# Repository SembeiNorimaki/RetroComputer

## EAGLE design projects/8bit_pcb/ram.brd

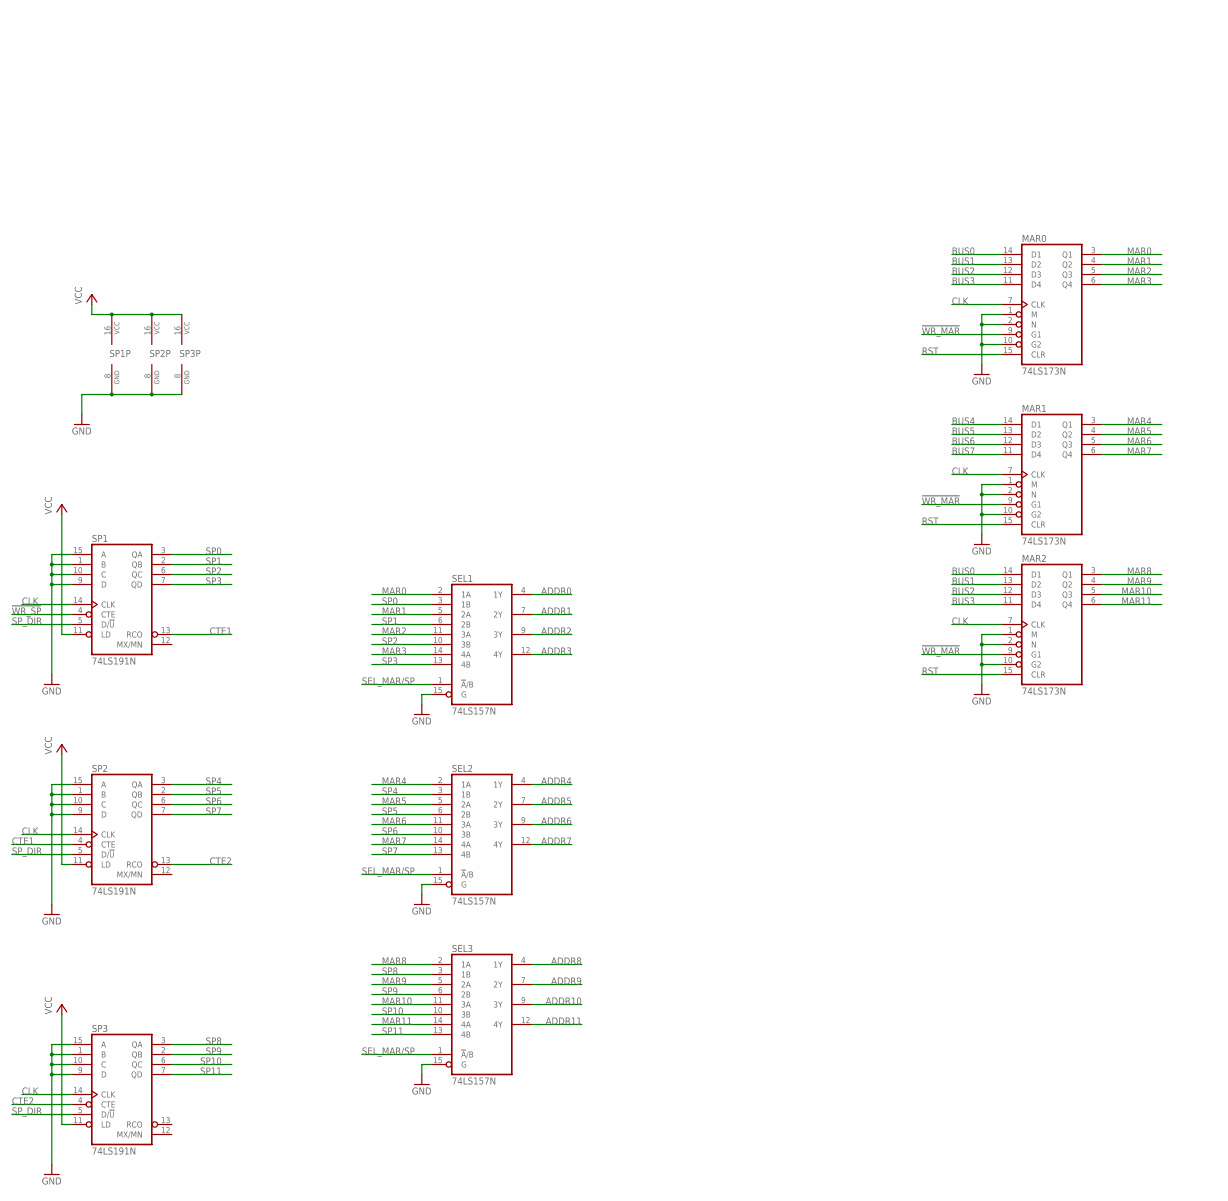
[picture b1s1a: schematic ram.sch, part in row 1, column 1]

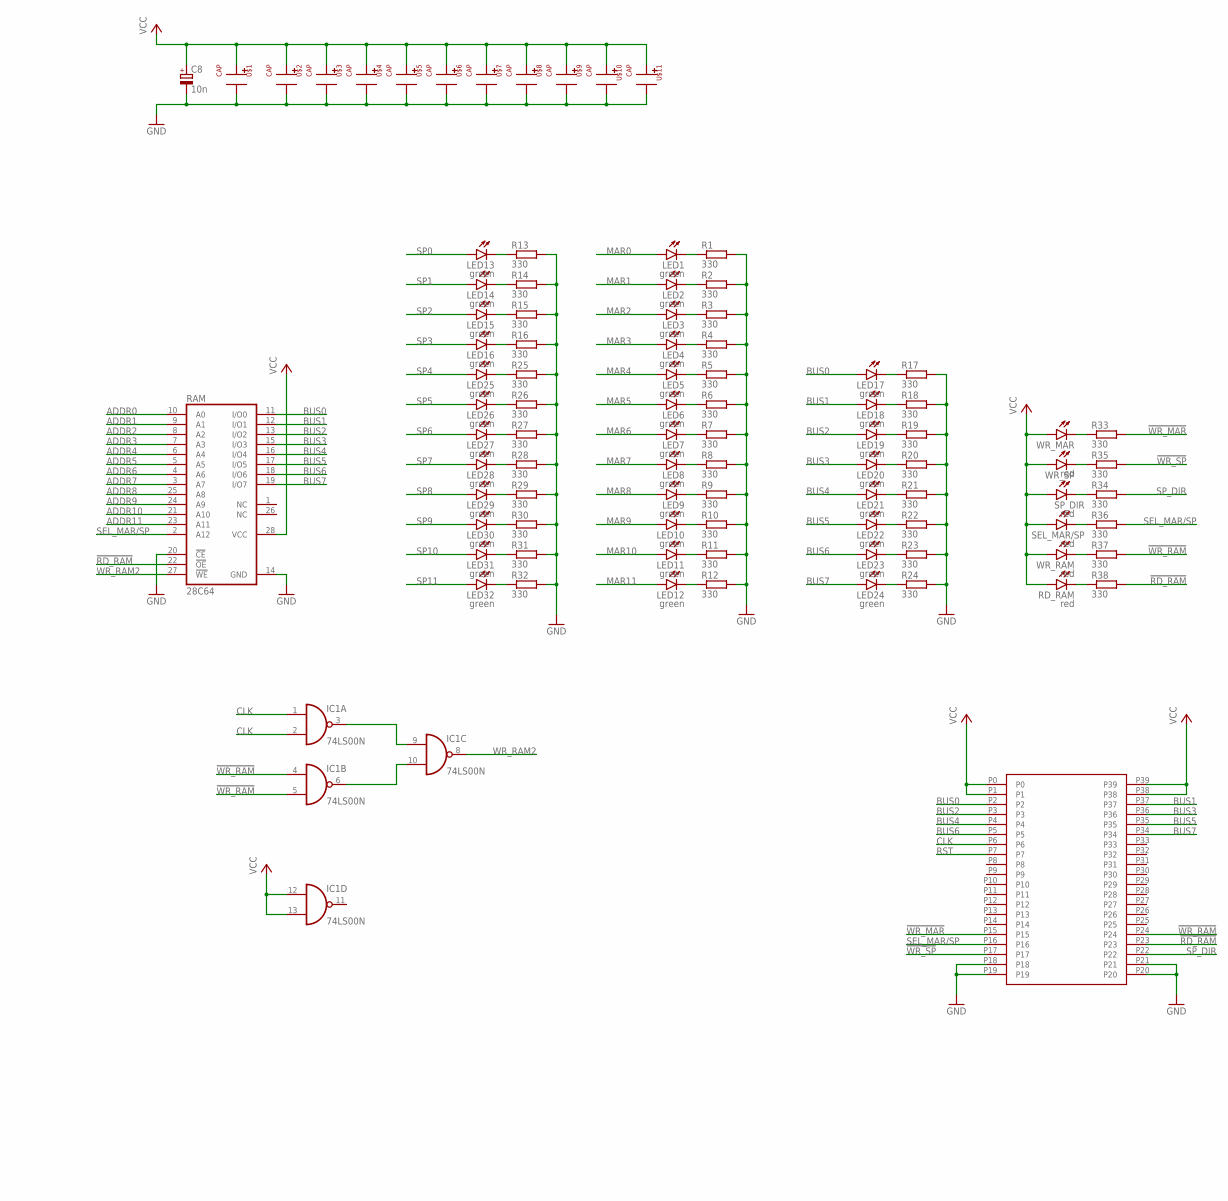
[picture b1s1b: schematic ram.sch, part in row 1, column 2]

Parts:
C8: 10n; E2,5-6E
IC1: 74LS00N; DIL14
LED1, LED2, LED3, LED4, LED5, LED6, LED7, LED8, LED9, LED10, LED11, LED12, LED13, LED14, LED15, LED16, LED17, LED18, LED19, LED20, LED21, LED22, LED23, LED24, LED25, LED26, LED27, LED28, LED29, LED30, LED31, LED32: green; SML1206
MAR0, MAR1, MAR2: 74LS173N; DIL16
R1, R2, R3, R4, R5, R6, R7, R8, R9, R10, R11, R12, R13, R14, R15, R16, R17, R18, R19, R20, R21, R22, R23, R24, R25, R26, R27, R28, R29, R30, R31, R32, R33, R34, R35, R36, R37, R38: 330; R0805
RAM: 28C64; DIL28-6
RD_RAM: red; SML1206
SEL1, SEL2, SEL3: 74LS157N; DIL16
SEL_MAR/SP: red; SML1206
SP1, SP2, SP3: 74LS191N; DIL16
SP_DIR: red; SML1206
U$1, U$2, U$3, U$4, U$5, U$6, U$7, U$8, U$9, U$10, U$11: CAP
U$12: 2X40
WR_MAR: red; SML1206
WR_RAM: red; SML1206
WR_SP: red; SML1206

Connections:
!RD_RAM: R38.2, RAM.22 (!OE), U$12.P23
!WR_MAR: MAR0.9 (G1), MAR1.9 (G1), MAR2.9 (G1), R33.2, U$12.P15
!WR_RAM: IC1.4 (I0), IC1.5 (I1), R37.2, U$12.P24
!WR_SP: R35.2, SP1.4 (CTE), U$12.P17
ADDR0: RAM.10 (A0), SEL1.4 (1Y)
ADDR1: RAM.9 (A1), SEL1.7 (2Y)
ADDR2: RAM.8 (A2), SEL1.9 (3Y)
ADDR3: RAM.7 (A3), SEL1.12 (4Y)
ADDR4: RAM.6 (A4), SEL2.4 (1Y)
ADDR5: RAM.5 (A5), SEL2.7 (2Y)
ADDR6: RAM.4 (A6), SEL2.9 (3Y)
ADDR7: RAM.3 (A7), SEL2.12 (4Y)
ADDR8: RAM.25 (A8), SEL3.4 (1Y)
ADDR9: RAM.24 (A9), SEL3.7 (2Y)
ADDR10: RAM.21 (A10), SEL3.9 (3Y)
ADDR11: RAM.23 (A11), SEL3.12 (4Y)
BUS0: LED17.A, MAR0.14 (D1), MAR2.14 (D1), RAM.11 (I/O0), U$12.P2
BUS1: LED18.A, MAR0.13 (D2), MAR2.13 (D2), RAM.12 (I/O1), U$12.P37
BUS2: LED19.A, MAR0.12 (D3), MAR2.12 (D3), RAM.13 (I/O2), U$12.P3
BUS3: LED20.A, MAR0.11 (D4), MAR2.11 (D4), RAM.15 (I/O3), U$12.P36
BUS4: LED21.A, MAR1.14 (D1), RAM.16 (I/O4), U$12.P4
BUS5: LED22.A, MAR1.13 (D2), RAM.17 (I/O5), U$12.P35
BUS6: LED23.A, MAR1.12 (D3), RAM.18 (I/O6), U$12.P5
BUS7: LED24.A, MAR1.11 (D4), RAM.19 (I/O7), U$12.P34
CLK: IC1.1 (I0), IC1.2 (I1), MAR0.7 (CLK), MAR1.7 (CLK), MAR2.7 (CLK), SP1.14 (CLK), SP2.14 (CLK), SP3.14 (CLK), U$12.P6
CTE1: SP1.13 (RCO), SP2.4 (CTE)
CTE2: SP2.13 (RCO), SP3.4 (CTE)
GND: C8.-, IC1.7 (GND), MAR0.1 (M), MAR0.2 (N), MAR0.8 (GND), MAR0.10 (G2), MAR1.1 (M), MAR1.2 (N), MAR1.8 (GND), MAR1.10 (G2), MAR2.1 (M), MAR2.2 (N), MAR2.8 (GND), MAR2.10 (G2), R1.2, R2.2, R3.2, R4.2, R5.2, R6.2, R7.2, R8.2, R9.2, R10.2, R11.2, R12.2, R13.2, R14.2, R15.2, R16.2, R17.2, R18.2, R19.2, R20.2, R21.2, R22.2, R23.2, R24.2, R25.2, R26.2, R27.2, R28.2, R29.2, R30.2, R31.2, R32.2, RAM.14 (GND), RAM.20 (!CE), SEL1.8 (GND), SEL1.15 (G), SEL2.8 (GND), SEL2.15 (G), SEL3.8 (GND), SEL3.15 (G), SP1.1 (B), SP1.8 (GND), SP1.9 (D), SP1.10 (C), SP1.15 (A), SP2.1 (B), SP2.8 (GND), SP2.9 (D), SP2.10 (C), SP2.15 (A), SP3.1 (B), SP3.8 (GND), SP3.9 (D), SP3.10 (C), SP3.15 (A), U$1.P-, U$2.P-, U$3.P-, U$4.P-, U$5.P-, U$6.P-, U$7.P-, U$8.P-, U$9.P-, U$10.P-, U$11.P-, U$12.P18, U$12.P19, U$12.P20, U$12.P21
MAR0: LED1.A, MAR0.3 (Q1), SEL1.2 (1A)
MAR1: LED2.A, MAR0.4 (Q2), SEL1.5 (2A)
MAR2: LED3.A, MAR0.5 (Q3), SEL1.11 (3A)
MAR3: LED4.A, MAR0.6 (Q4), SEL1.14 (4A)
MAR4: LED5.A, MAR1.3 (Q1), SEL2.2 (1A)
MAR5: LED6.A, MAR1.4 (Q2), SEL2.5 (2A)
MAR6: LED7.A, MAR1.5 (Q3), SEL2.11 (3A)
MAR7: LED8.A, MAR1.6 (Q4), SEL2.14 (4A)
MAR8: LED9.A, MAR2.3 (Q1), SEL3.2 (1A)
MAR9: LED10.A, MAR2.4 (Q2), SEL3.5 (2A)
MAR10: LED11.A, MAR2.5 (Q3), SEL3.11 (3A)
MAR11: LED12.A, MAR2.6 (Q4), SEL3.14 (4A)
unnamed: LED1.C, R1.1
unnamed: LED2.C, R2.1
unnamed: LED3.C, R3.1
unnamed: LED4.C, R4.1
unnamed: LED5.C, R5.1
unnamed: LED6.C, R6.1
unnamed: LED7.C, R7.1
unnamed: LED8.C, R8.1
unnamed: LED13.C, R13.1
unnamed: LED9.C, R9.1
unnamed: LED10.C, R10.1
unnamed: LED11.C, R11.1
unnamed: LED12.C, R12.1
unnamed: LED14.C, R14.1
unnamed: LED15.C, R15.1
unnamed: LED16.C, R16.1
unnamed: LED25.C, R25.1
unnamed: LED26.C, R26.1
unnamed: LED17.C, R17.1
unnamed: LED18.C, R18.1
unnamed: LED19.C, R19.1
unnamed: LED20.C, R20.1
unnamed: LED21.C, R21.1
unnamed: LED22.C, R22.1
unnamed: LED23.C, R23.1
unnamed: LED24.C, R24.1
unnamed: LED27.C, R27.1
unnamed: LED28.C, R28.1
unnamed: LED29.C, R29.1
unnamed: LED30.C, R30.1
unnamed: LED31.C, R31.1
unnamed: LED32.C, R32.1
unnamed: IC1.3 (O), IC1.9 (I0)
unnamed: IC1.6 (O), IC1.10 (I1)
unnamed: R36.1, SEL_MAR/SP.C
unnamed: R33.1, WR_MAR.C
unnamed: R34.1, SP_DIR.C
unnamed: R35.1, WR_SP.C
unnamed: R37.1, WR_RAM.C
unnamed: R38.1, RD_RAM.C
RST: MAR0.15 (CLR), MAR1.15 (CLR), MAR2.15 (CLR), U$12.P7
SEL_MAR/SP: R36.2, RAM.2 (A12), SEL1.1 (!A!/B), SEL2.1 (!A!/B), SEL3.1 (!A!/B), U$12.P16
SP0: LED13.A, SEL1.3 (1B), SP1.3 (QA)
SP1: LED14.A, SEL1.6 (2B), SP1.2 (QB)
SP2: LED15.A, SEL1.10 (3B), SP1.6 (QC)
SP3: LED16.A, SEL1.13 (4B), SP1.7 (QD)
SP4: LED25.A, SEL2.3 (1B), SP2.3 (QA)
SP5: LED26.A, SEL2.6 (2B), SP2.2 (QB)
SP6: LED27.A, SEL2.10 (3B), SP2.6 (QC)
SP7: LED28.A, SEL2.13 (4B), SP2.7 (QD)
SP8: LED29.A, SEL3.3 (1B), SP3.3 (QA)
SP9: LED30.A, SEL3.6 (2B), SP3.2 (QB)
SP10: LED31.A, SEL3.10 (3B), SP3.6 (QC)
SP11: LED32.A, SEL3.13 (4B), SP3.7 (QD)
SP_DIR: R34.2, SP1.5 (D/!U), SP2.5 (D/!U), SP3.5 (D/!U), U$12.P22
VCC: C8.+, IC1.12 (I0), IC1.13 (I1), IC1.14 (VCC), MAR0.16 (VCC), MAR1.16 (VCC), MAR2.16 (VCC), RAM.28 (VCC), RD_RAM.A, SEL1.16 (VCC), SEL2.16 (VCC), SEL3.16 (VCC), SEL_MAR/SP.A, SP1.11 (LD), SP1.16 (VCC), SP2.11 (LD), SP2.16 (VCC), SP3.11 (LD), SP3.16 (VCC), SP_DIR.A, U$1.P+, U$2.P+, U$3.P+, U$4.P+, U$5.P+, U$6.P+, U$7.P+, U$8.P+, U$9.P+, U$10.P+, U$11.P+, U$12.P0, U$12.P1, U$12.P38, U$12.P39, WR_MAR.A, WR_RAM.A, WR_SP.A
WR_RAM2: IC1.8 (O), RAM.27 (!WE)

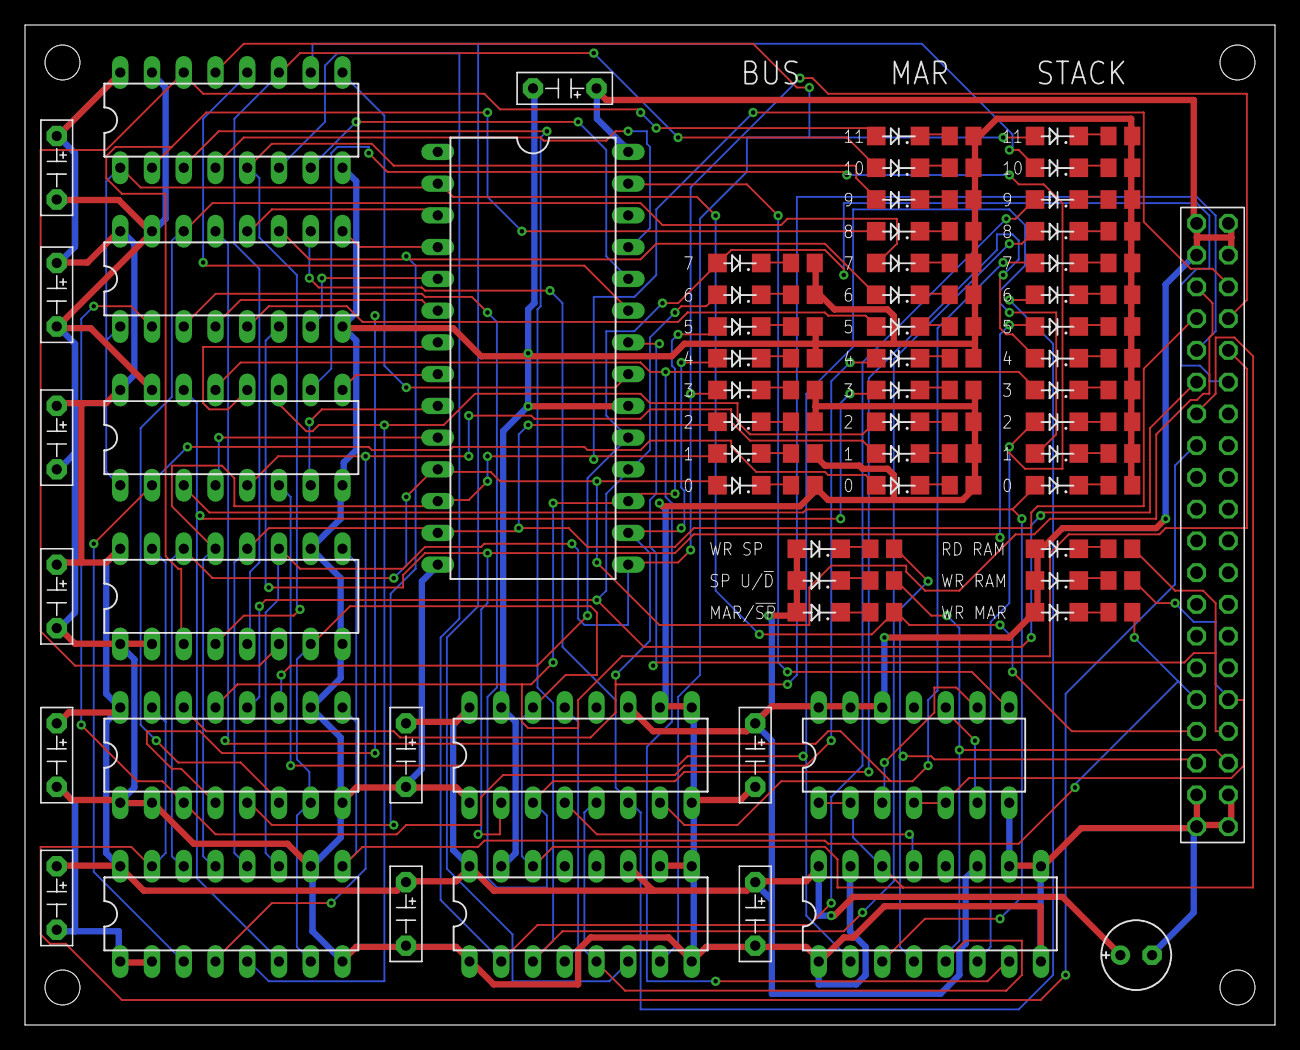
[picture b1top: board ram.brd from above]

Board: 2 copper layers, 100.0 x 80.0 mm, 100 parts (0 on the bottom side), 97 nets.

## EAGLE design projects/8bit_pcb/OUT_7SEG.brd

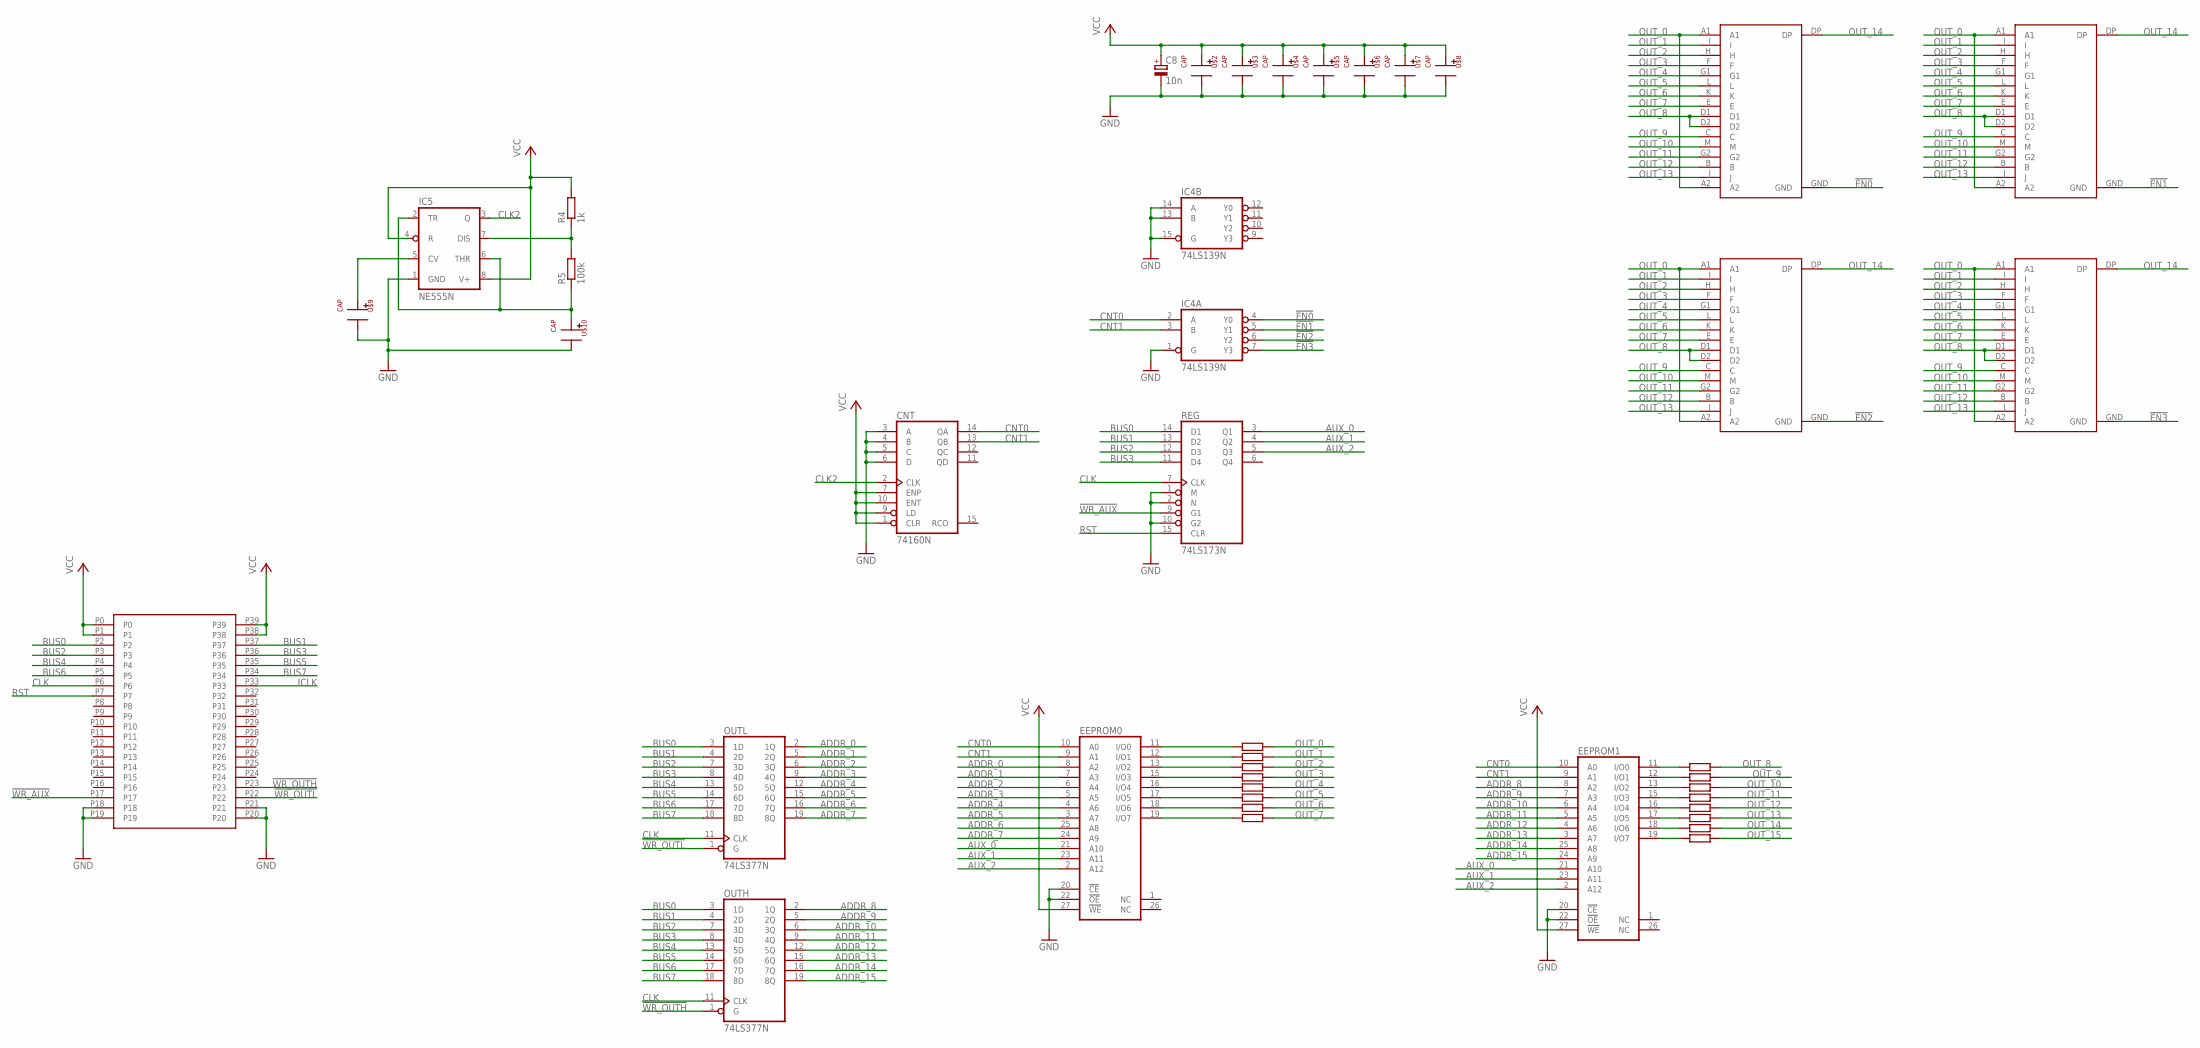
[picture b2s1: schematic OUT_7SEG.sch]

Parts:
C8: 10n; E2,5-6E
CNT: 74160N; DIL16
DISP1, DISP2, DISP3, DISP4: 16SEG
EEPROM0, EEPROM1: 78C64P; DIL28-6
IC4: 74LS139N; DIL16
IC5: NE555N; DIL08
OUTH: 74LS377N; DIL20
OUTL: 74LS377N; DIL20
R1, R2, R3, R6, R7, R8, R9, R10, R11, R12, R13, R14, R15, R16, R17, R41: 330; R0805
R4: 1k; 0204/7
R5: 100k; 0204/7
REG: 74LS173N; DIL16
U$1: 2X40
U$2, U$3, U$4, U$5, U$6, U$7, U$8, U$9, U$10: CAP

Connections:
!EN0: DISP1.GND, IC4.4 (Y0)
!EN1: DISP2.GND, IC4.5 (Y1)
!EN2: DISP3.GND, IC4.6 (Y2)
!EN3: DISP4.GND, IC4.7 (Y3)
!WR_AUX: REG.9 (G1), U$1.P17
!WR_OUTH: OUTH.1 (G), U$1.P23
!WR_OUTL: OUTL.1 (G), U$1.P22
ADDR_0: EEPROM0.8 (A2), OUTL.2 (1Q)
ADDR_1: EEPROM0.7 (A3), OUTL.5 (2Q)
ADDR_2: EEPROM0.6 (A4), OUTL.6 (3Q)
ADDR_3: EEPROM0.5 (A5), OUTL.9 (4Q)
ADDR_4: EEPROM0.4 (A6), OUTL.12 (5Q)
ADDR_5: EEPROM0.3 (A7), OUTL.15 (6Q)
ADDR_6: EEPROM0.25 (A8), OUTL.16 (7Q)
ADDR_7: EEPROM0.24 (A9), OUTL.19 (8Q)
ADDR_8: EEPROM1.8 (A2), OUTH.2 (1Q)
ADDR_9: EEPROM1.7 (A3), OUTH.5 (2Q)
ADDR_10: EEPROM1.6 (A4), OUTH.6 (3Q)
ADDR_11: EEPROM1.5 (A5), OUTH.9 (4Q)
ADDR_12: EEPROM1.4 (A6), OUTH.12 (5Q)
ADDR_13: EEPROM1.3 (A7), OUTH.15 (6Q)
ADDR_14: EEPROM1.25 (A8), OUTH.16 (7Q)
ADDR_15: EEPROM1.24 (A9), OUTH.19 (8Q)
AUX_0: EEPROM0.21 (A10), EEPROM1.21 (A10), REG.3 (Q1)
AUX_1: EEPROM0.23 (A11), EEPROM1.23 (A11), REG.4 (Q2)
AUX_2: EEPROM0.2 (A12), EEPROM1.2 (A12), REG.5 (Q3)
BUS0: OUTH.3 (1D), OUTL.3 (1D), REG.14 (D1), U$1.P2
BUS1: OUTH.4 (2D), OUTL.4 (2D), REG.13 (D2), U$1.P37
BUS2: OUTH.7 (3D), OUTL.7 (3D), REG.12 (D3), U$1.P3
BUS3: OUTH.8 (4D), OUTL.8 (4D), REG.11 (D4), U$1.P36
BUS4: OUTH.13 (5D), OUTL.13 (5D), U$1.P4
BUS5: OUTH.14 (6D), OUTL.14 (6D), U$1.P35
BUS6: OUTH.17 (7D), OUTL.17 (7D), U$1.P5
BUS7: OUTH.18 (8D), OUTL.18 (8D), U$1.P34
CLK: OUTH.11 (CLK), OUTL.11 (CLK), REG.7 (CLK), U$1.P6
CLK2: CNT.2 (CLK), IC5.3 (Q)
CNT0: CNT.14 (QA), EEPROM0.10 (A0), EEPROM1.10 (A0), IC4.2 (A)
CNT1: CNT.13 (QB), EEPROM0.9 (A1), EEPROM1.9 (A1), IC4.3 (B)
GND: C8.-, CNT.3 (A), CNT.4 (B), CNT.5 (C), CNT.6 (D), CNT.8 (GND), EEPROM0.14 (GND), EEPROM0.20 (!CE), EEPROM0.22 (!OE), EEPROM1.14 (GND), EEPROM1.20 (!CE), EEPROM1.22 (!OE), IC4.1 (G), IC4.8 (GND), IC4.13 (B), IC4.14 (A), IC4.15 (G), IC5.1 (GND), OUTH.10 (GND), OUTL.10 (GND), REG.1 (M), REG.2 (N), REG.8 (GND), REG.10 (G2), U$1.P18, U$1.P19, U$1.P20, U$1.P21, U$2.P-, U$3.P-, U$4.P-, U$5.P-, U$6.P-, U$7.P-, U$8.P-, U$9.P-, U$10.P-
ICLK: U$1.P33
unnamed: IC5.7 (DIS), R4.1, R5.2
unnamed: IC5.5 (CV), U$9.P+
unnamed: EEPROM1.11 (I/O0), R41.1
unnamed: EEPROM1.12 (I/O1), R1.1
unnamed: EEPROM1.13 (I/O2), R2.1
unnamed: EEPROM1.15 (I/O3), R3.1
unnamed: EEPROM1.16 (I/O4), R6.1
unnamed: EEPROM1.17 (I/O5), R7.1
unnamed: EEPROM1.18 (I/O6), R8.1
unnamed: EEPROM1.19 (I/O7), R9.1
unnamed: EEPROM0.11 (I/O0), R10.1
unnamed: EEPROM0.12 (I/O1), R11.1
unnamed: EEPROM0.13 (I/O2), R12.1
unnamed: EEPROM0.15 (I/O3), R13.1
unnamed: EEPROM0.16 (I/O4), R14.1
unnamed: EEPROM0.17 (I/O5), R16.1
unnamed: EEPROM0.18 (I/O6), R15.1
unnamed: EEPROM0.19 (I/O7), R17.1
unnamed: IC5.2 (TR), IC5.6 (THR), R5.1, U$10.P+
OUT_0: DISP1.A1, DISP1.A2, DISP2.A1, DISP2.A2, DISP3.A1, DISP3.A2, DISP4.A1, DISP4.A2, R10.2
OUT_1: DISP1.I, DISP2.I, DISP3.I, DISP4.I, R11.2
OUT_2: DISP1.H, DISP2.H, DISP3.H, DISP4.H, R12.2
OUT_3: DISP1.F, DISP2.F, DISP3.F, DISP4.F, R13.2
OUT_4: DISP1.G1, DISP2.G1, DISP3.G1, DISP4.G1, R14.2
OUT_5: DISP1.L, DISP2.L, DISP3.L, DISP4.L, R16.2
OUT_6: DISP1.K, DISP2.K, DISP3.K, DISP4.K, R15.2
OUT_7: DISP1.E, DISP2.E, DISP3.E, DISP4.E, R17.2
OUT_8: DISP1.D1, DISP1.D2, DISP2.D1, DISP2.D2, DISP3.D1, DISP3.D2, DISP4.D1, DISP4.D2, R41.2
OUT_9: DISP1.C, DISP2.C, DISP3.C, DISP4.C, R1.2
OUT_10: DISP1.M, DISP2.M, DISP3.M, DISP4.M, R2.2
OUT_11: DISP1.G2, DISP2.G2, DISP3.G2, DISP4.G2, R3.2
OUT_12: DISP1.B, DISP2.B, DISP3.B, DISP4.B, R6.2
OUT_13: DISP1.J, DISP2.J, DISP3.J, DISP4.J, R7.2
OUT_14: DISP1.DP, DISP2.DP, DISP3.DP, DISP4.DP, R8.2
OUT_15: R9.2
RST: REG.15 (CLR), U$1.P7
VCC: C8.+, CNT.1 (CLR), CNT.7 (ENP), CNT.9 (LD), CNT.10 (ENT), CNT.16 (VCC), EEPROM0.27 (!WE), EEPROM0.28 (VCC), EEPROM1.27 (!WE), EEPROM1.28 (VCC), IC4.16 (VCC), IC5.4 (R), IC5.8 (V+), OUTH.20 (VCC), OUTL.20 (VCC), R4.2, REG.16 (VCC), U$1.P0, U$1.P1, U$1.P38, U$1.P39, U$2.P+, U$3.P+, U$4.P+, U$5.P+, U$6.P+, U$7.P+, U$8.P+

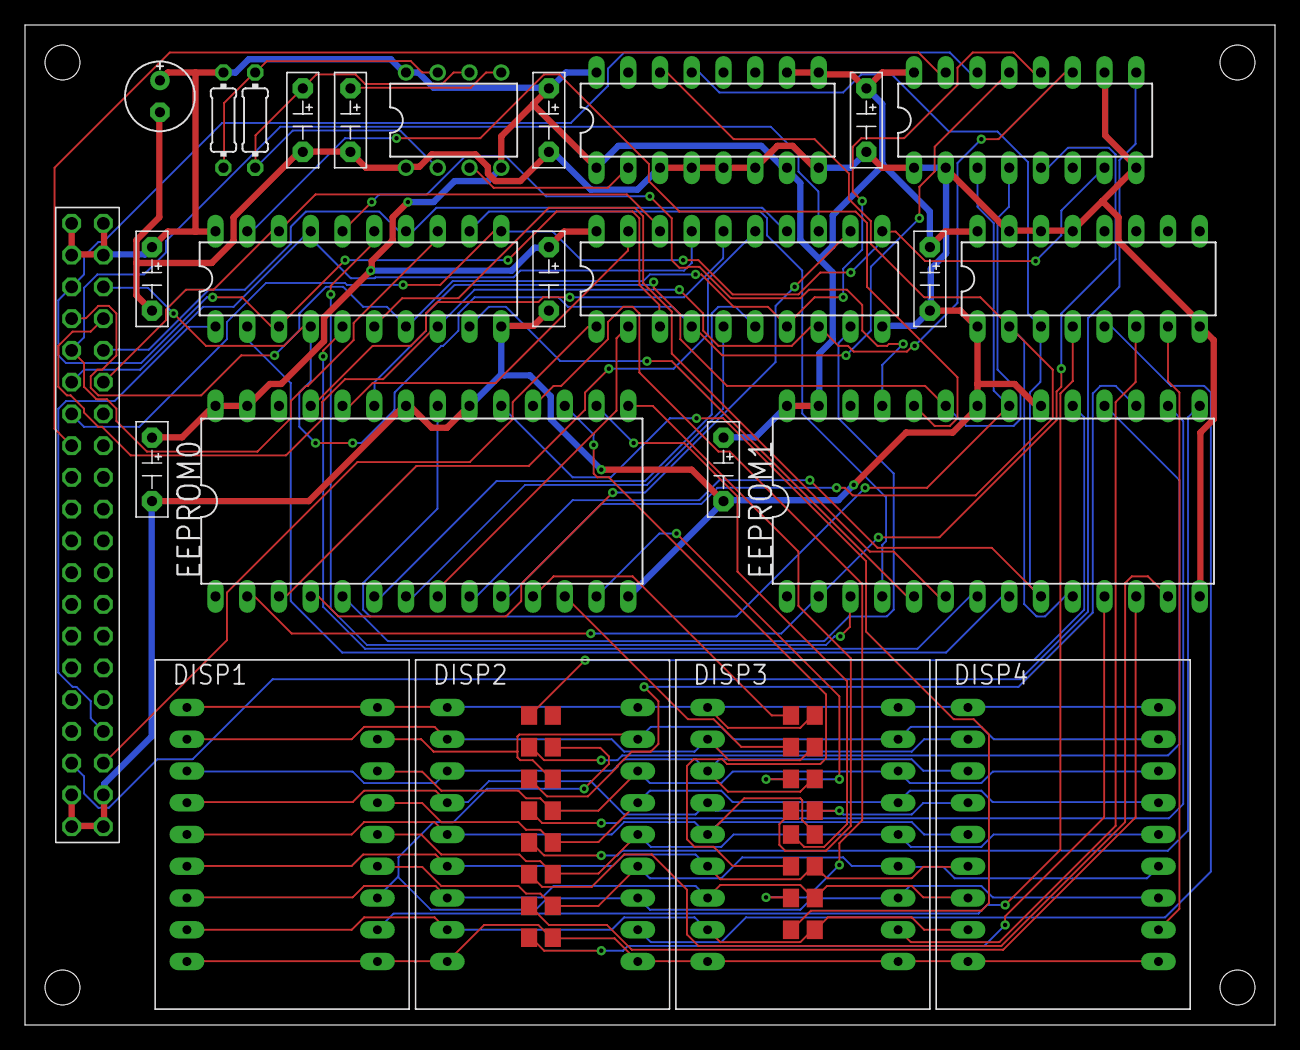
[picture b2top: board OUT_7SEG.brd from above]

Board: 2 copper layers, 100.0 x 80.0 mm, 41 parts (0 on the bottom side), 75 nets.

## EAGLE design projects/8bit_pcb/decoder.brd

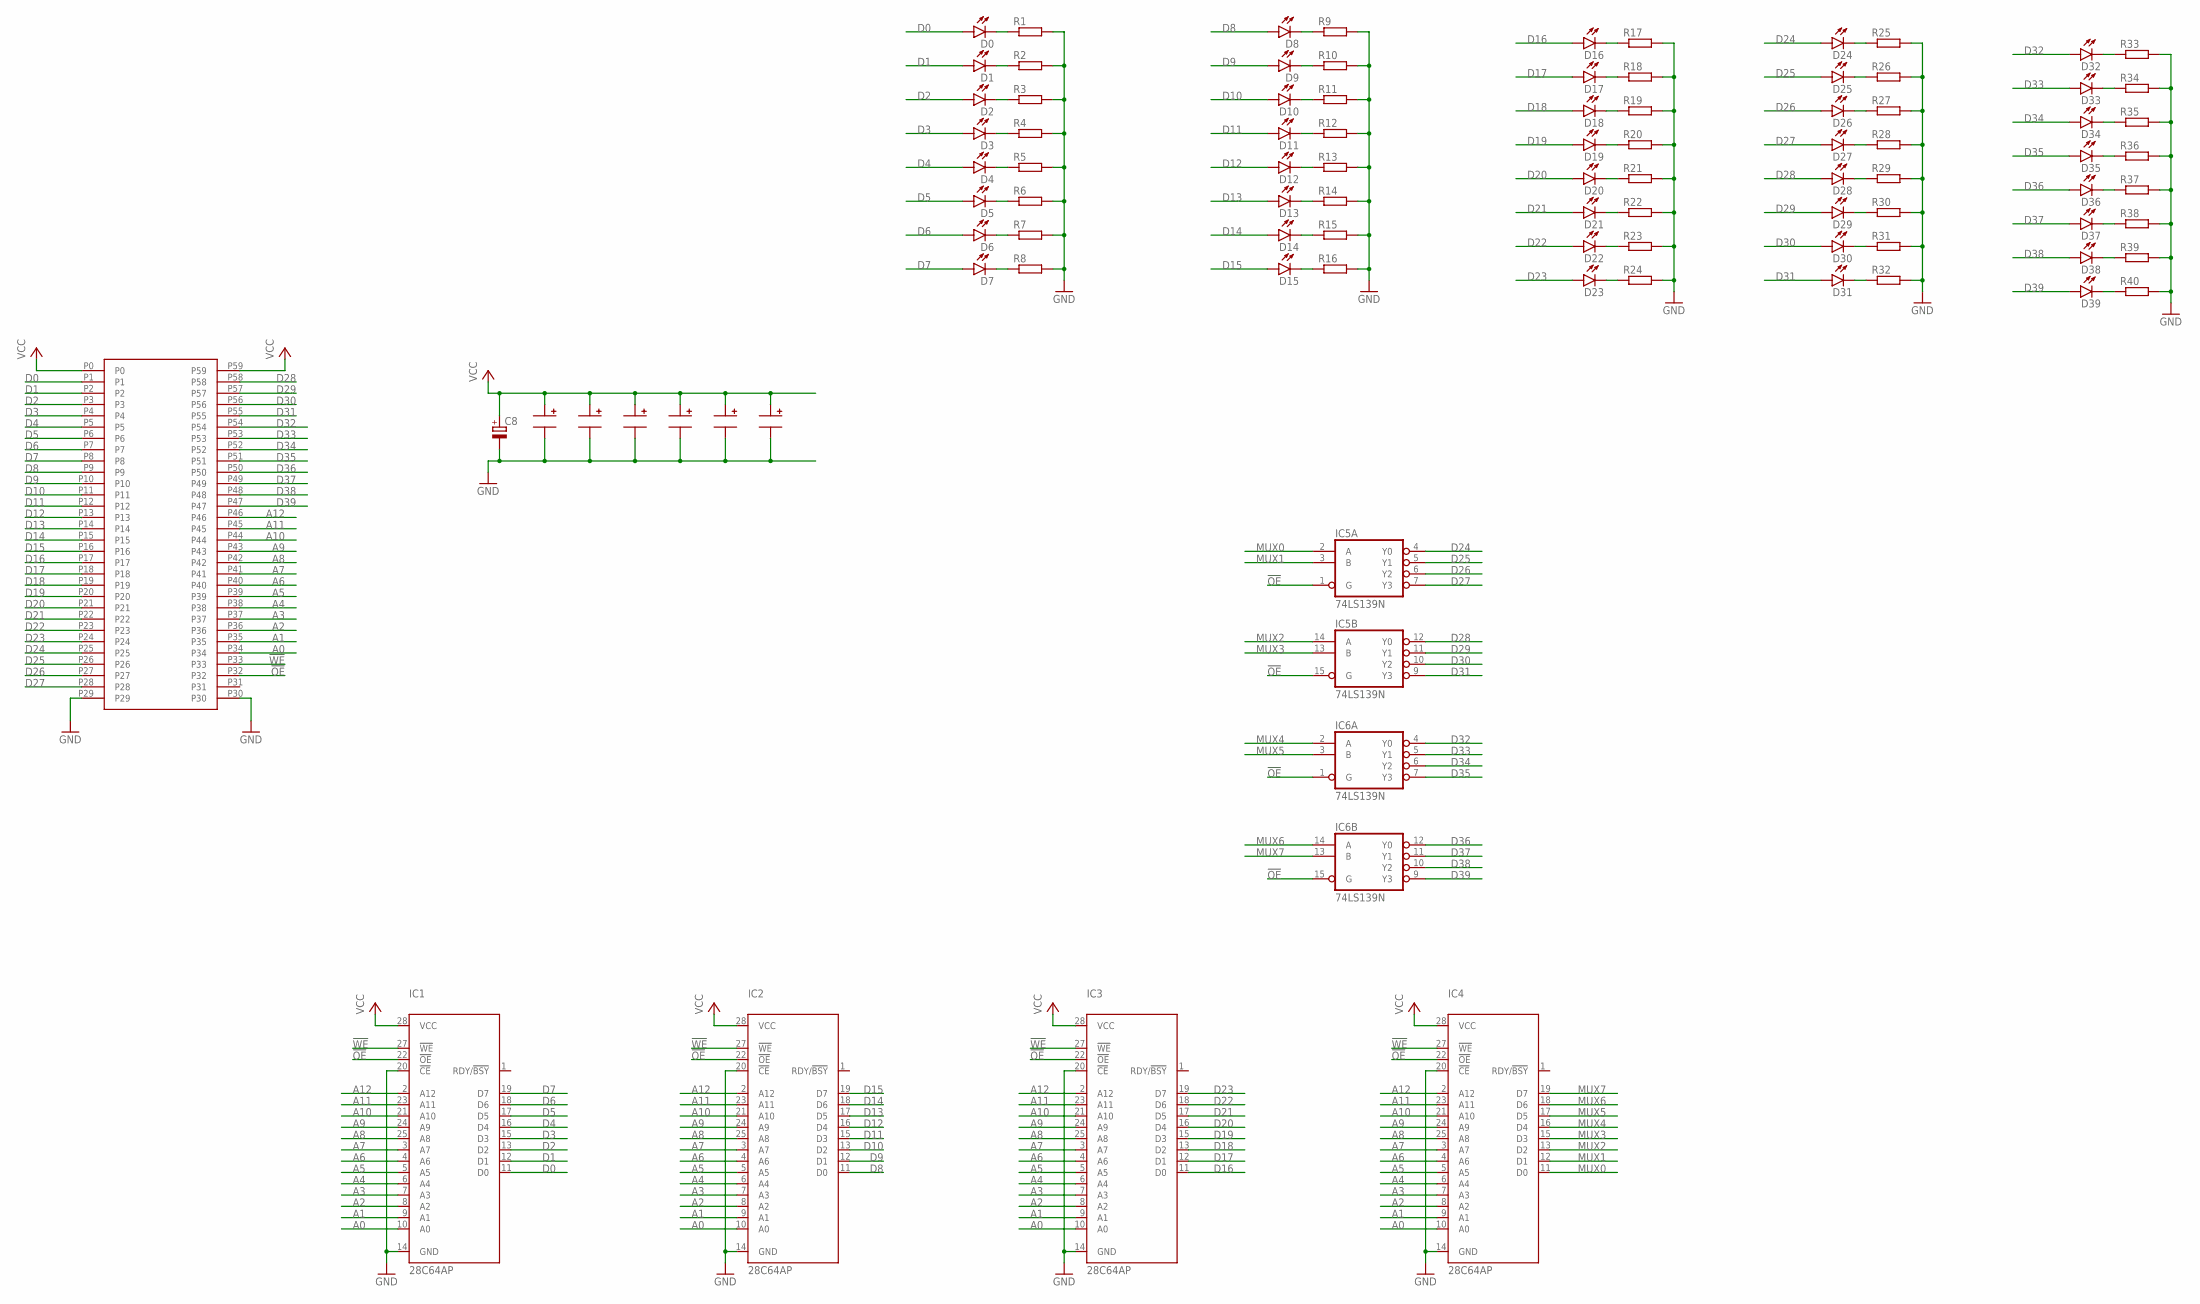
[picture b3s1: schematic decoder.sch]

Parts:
C8: CPOL-EUE2,5-6E; E2,5-6E
D0, D1, D2, D3, D4, D5, D6, D7, D8, D9, D10, D11, D12, D13, D14, D15, D16, D17, D18, D19, D20, D21, D22, D23, D24, D25, D26, D27, D28, D29, D30, D31, D32, D33, D34, D35, D36, D37, D38, D39: LEDSML1206; SML1206
IC1, IC2, IC3, IC4: 28C64AP; DIL28-6
IC5, IC6: 74LS139N; DIL16
R1, R2, R3, R4, R5, R6, R7, R8, R9, R10, R11, R12, R13, R14, R15, R16, R17, R18, R19, R20, R21, R22, R23, R24, R25, R26, R27, R28, R29, R30, R31, R32, R33, R34, R35, R36, R37, R38, R39, R40: R-EU_R0805; R0805
U$1: 2X60
U$2, U$3, U$4, U$5, U$6, U$7: CAP

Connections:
!OE: IC1.22 (!OE), IC2.22 (!OE), IC3.22 (!OE), IC4.22 (!OE), IC5.1 (G), IC5.15 (G), IC6.1 (G), IC6.15 (G), U$1.P32
!WE: IC1.27 (!WE), IC2.27 (!WE), IC3.27 (!WE), IC4.27 (!WE), U$1.P33
A0: IC1.10 (A0), IC2.10 (A0), IC3.10 (A0), IC4.10 (A0), U$1.P34
A1: IC1.9 (A1), IC2.9 (A1), IC3.9 (A1), IC4.9 (A1), U$1.P35
A2: IC1.8 (A2), IC2.8 (A2), IC3.8 (A2), IC4.8 (A2), U$1.P36
A3: IC1.7 (A3), IC2.7 (A3), IC3.7 (A3), IC4.7 (A3), U$1.P37
A4: IC1.6 (A4), IC2.6 (A4), IC3.6 (A4), IC4.6 (A4), U$1.P38
A5: IC1.5 (A5), IC2.5 (A5), IC3.5 (A5), IC4.5 (A5), U$1.P39
A6: IC1.4 (A6), IC2.4 (A6), IC3.4 (A6), IC4.4 (A6), U$1.P40
A7: IC1.3 (A7), IC2.3 (A7), IC3.3 (A7), IC4.3 (A7), U$1.P41
A8: IC1.25 (A8), IC2.25 (A8), IC3.25 (A8), IC4.25 (A8), U$1.P42
A9: IC1.24 (A9), IC2.24 (A9), IC3.24 (A9), IC4.24 (A9), U$1.P43
A10: IC1.21 (A10), IC2.21 (A10), IC3.21 (A10), IC4.21 (A10), U$1.P44
A11: IC1.23 (A11), IC2.23 (A11), IC3.23 (A11), IC4.23 (A11), U$1.P45
A12: IC1.2 (A12), IC2.2 (A12), IC3.2 (A12), IC4.2 (A12), U$1.P46
D0: D0.A, IC1.11 (D0), U$1.P1
D1: D1.A, IC1.12 (D1), U$1.P2
D2: D2.A, IC1.13 (D2), U$1.P3
D3: D3.A, IC1.15 (D3), U$1.P4
D4: D4.A, IC1.16 (D4), U$1.P5
D5: D5.A, IC1.17 (D5), U$1.P6
D6: D6.A, IC1.18 (D6), U$1.P7
D7: D7.A, IC1.19 (D7), U$1.P8
D8: D8.A, IC2.11 (D0), U$1.P9
D9: D9.A, IC2.12 (D1), U$1.P10
D10: D10.A, IC2.13 (D2), U$1.P11
D11: D11.A, IC2.15 (D3), U$1.P12
D12: D12.A, IC2.16 (D4), U$1.P13
D13: D13.A, IC2.17 (D5), U$1.P14
D14: D14.A, IC2.18 (D6), U$1.P15
D15: D15.A, IC2.19 (D7), U$1.P16
D16: D16.A, IC3.11 (D0), U$1.P17
D17: D17.A, IC3.12 (D1), U$1.P18
D18: D18.A, IC3.13 (D2), U$1.P19
D19: D19.A, IC3.15 (D3), U$1.P20
D20: D20.A, IC3.16 (D4), U$1.P21
D21: D21.A, IC3.17 (D5), U$1.P22
D22: D22.A, IC3.18 (D6), U$1.P23
D23: D23.A, IC3.19 (D7), U$1.P24
D24: D24.A, IC5.4 (Y0), U$1.P25
D25: D25.A, IC5.5 (Y1), U$1.P26
D26: D26.A, IC5.6 (Y2), U$1.P27
D27: D27.A, IC5.7 (Y3), U$1.P28
D28: D28.A, IC5.12 (Y0), U$1.P58
D29: D29.A, IC5.11 (Y1), U$1.P57
D30: D30.A, IC5.10 (Y2), U$1.P56
D31: D31.A, IC5.9 (Y3), U$1.P55
D32: D32.A, IC6.4 (Y0), U$1.P54
D33: D33.A, IC6.5 (Y1), U$1.P53
D34: D34.A, IC6.6 (Y2), U$1.P52
D35: D35.A, IC6.7 (Y3), U$1.P51
D36: D36.A, IC6.12 (Y0), U$1.P50
D37: D37.A, IC6.11 (Y1), U$1.P49
D38: D38.A, IC6.10 (Y2), U$1.P48
D39: D39.A, IC6.9 (Y3), U$1.P47
GND: C8.-, IC1.14 (GND), IC1.20 (!CE), IC2.14 (GND), IC2.20 (!CE), IC3.14 (GND), IC3.20 (!CE), IC4.14 (GND), IC4.20 (!CE), IC5.8 (GND), IC6.8 (GND), R1.2, R2.2, R3.2, R4.2, R5.2, R6.2, R7.2, R8.2, R9.2, R10.2, R11.2, R12.2, R13.2, R14.2, R15.2, R16.2, R17.2, R18.2, R19.2, R20.2, R21.2, R22.2, R23.2, R24.2, R25.2, R26.2, R27.2, R28.2, R29.2, R30.2, R31.2, R32.2, R33.2, R34.2, R35.2, R36.2, R37.2, R38.2, R39.2, R40.2, U$1.P29, U$1.P30, U$2.P-, U$3.P-, U$4.P-, U$5.P-, U$6.P-, U$7.P-
MUX0: IC4.11 (D0), IC5.2 (A)
MUX1: IC4.12 (D1), IC5.3 (B)
MUX2: IC4.13 (D2), IC5.14 (A)
MUX3: IC4.15 (D3), IC5.13 (B)
MUX4: IC4.16 (D4), IC6.2 (A)
MUX5: IC4.17 (D5), IC6.3 (B)
MUX6: IC4.18 (D6), IC6.14 (A)
MUX7: IC4.19 (D7), IC6.13 (B)
unnamed: D0.C, R1.1
unnamed: D1.C, R2.1
unnamed: D2.C, R3.1
unnamed: D3.C, R4.1
unnamed: D4.C, R5.1
unnamed: D5.C, R6.1
unnamed: D6.C, R7.1
unnamed: D7.C, R8.1
unnamed: D8.C, R9.1
unnamed: D9.C, R10.1
unnamed: D10.C, R11.1
unnamed: D11.C, R12.1
unnamed: D32.C, R33.1
unnamed: D33.C, R34.1
unnamed: D12.C, R13.1
unnamed: D13.C, R14.1
unnamed: D14.C, R15.1
unnamed: D15.C, R16.1
unnamed: D16.C, R17.1
unnamed: D17.C, R18.1
unnamed: D18.C, R19.1
unnamed: D19.C, R20.1
unnamed: D20.C, R21.1
unnamed: D34.C, R35.1
unnamed: D35.C, R36.1
unnamed: D23.C, R24.1
unnamed: D22.C, R23.1
unnamed: D21.C, R22.1
unnamed: D36.C, R37.1
unnamed: D37.C, R38.1
unnamed: D38.C, R39.1
unnamed: D39.C, R40.1
unnamed: D24.C, R25.1
unnamed: D25.C, R26.1
unnamed: D26.C, R27.1
unnamed: D27.C, R28.1
unnamed: D28.C, R29.1
unnamed: D29.C, R30.1
unnamed: D30.C, R31.1
unnamed: D31.C, R32.1
VCC: C8.+, IC1.28 (VCC), IC2.28 (VCC), IC3.28 (VCC), IC4.28 (VCC), IC5.16 (VCC), IC6.16 (VCC), U$1.P0, U$1.P59, U$2.P+, U$3.P+, U$4.P+, U$5.P+, U$6.P+, U$7.P+

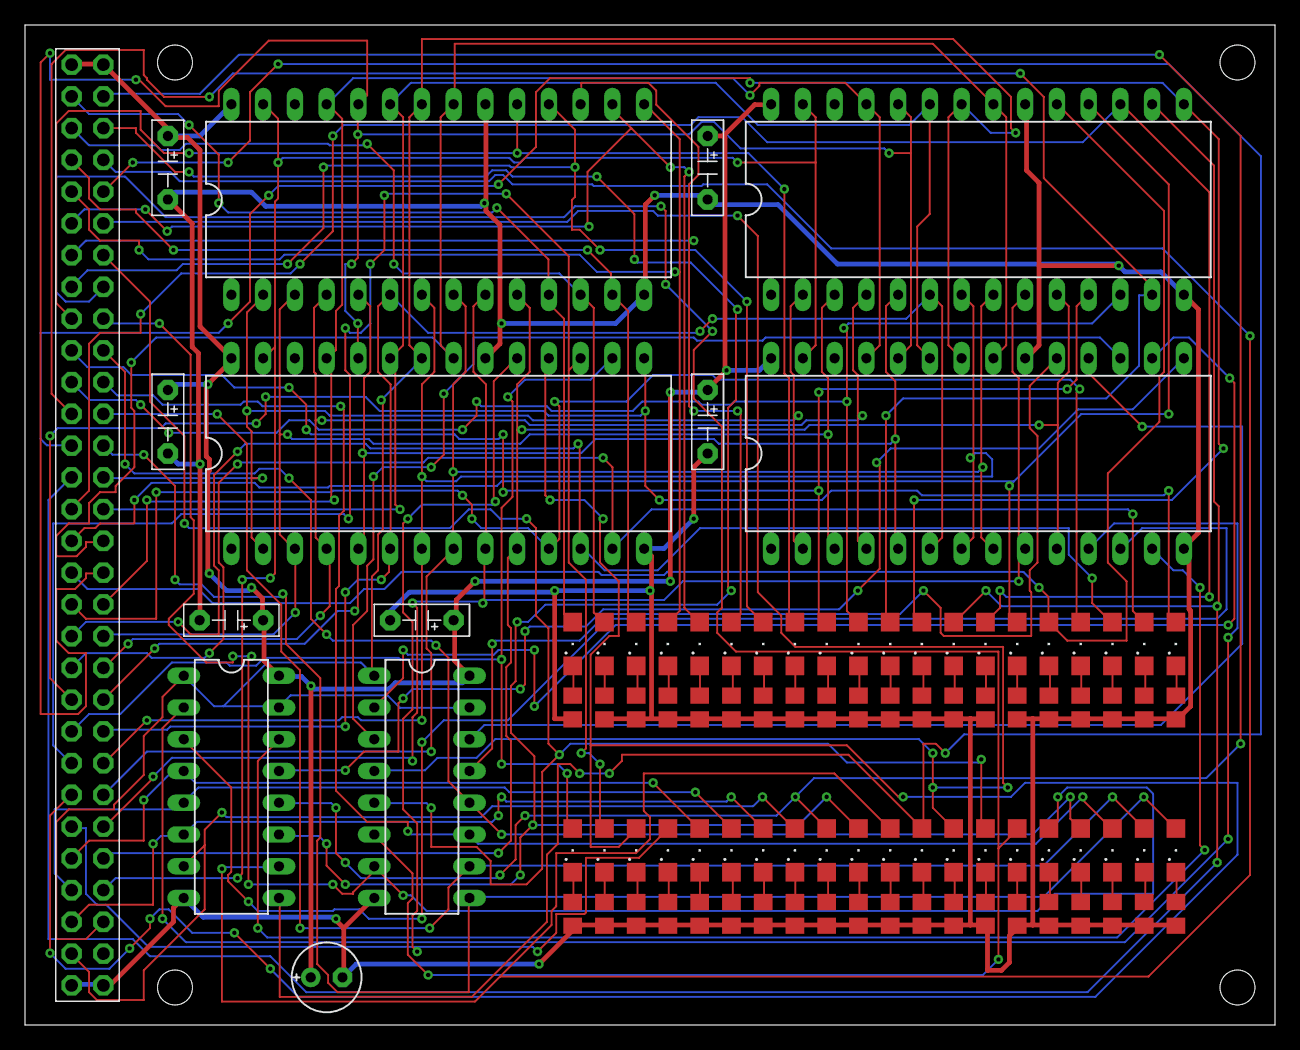
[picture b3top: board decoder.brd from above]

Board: 2 copper layers, 100.0 x 80.0 mm, 94 parts (0 on the bottom side), 105 nets.
